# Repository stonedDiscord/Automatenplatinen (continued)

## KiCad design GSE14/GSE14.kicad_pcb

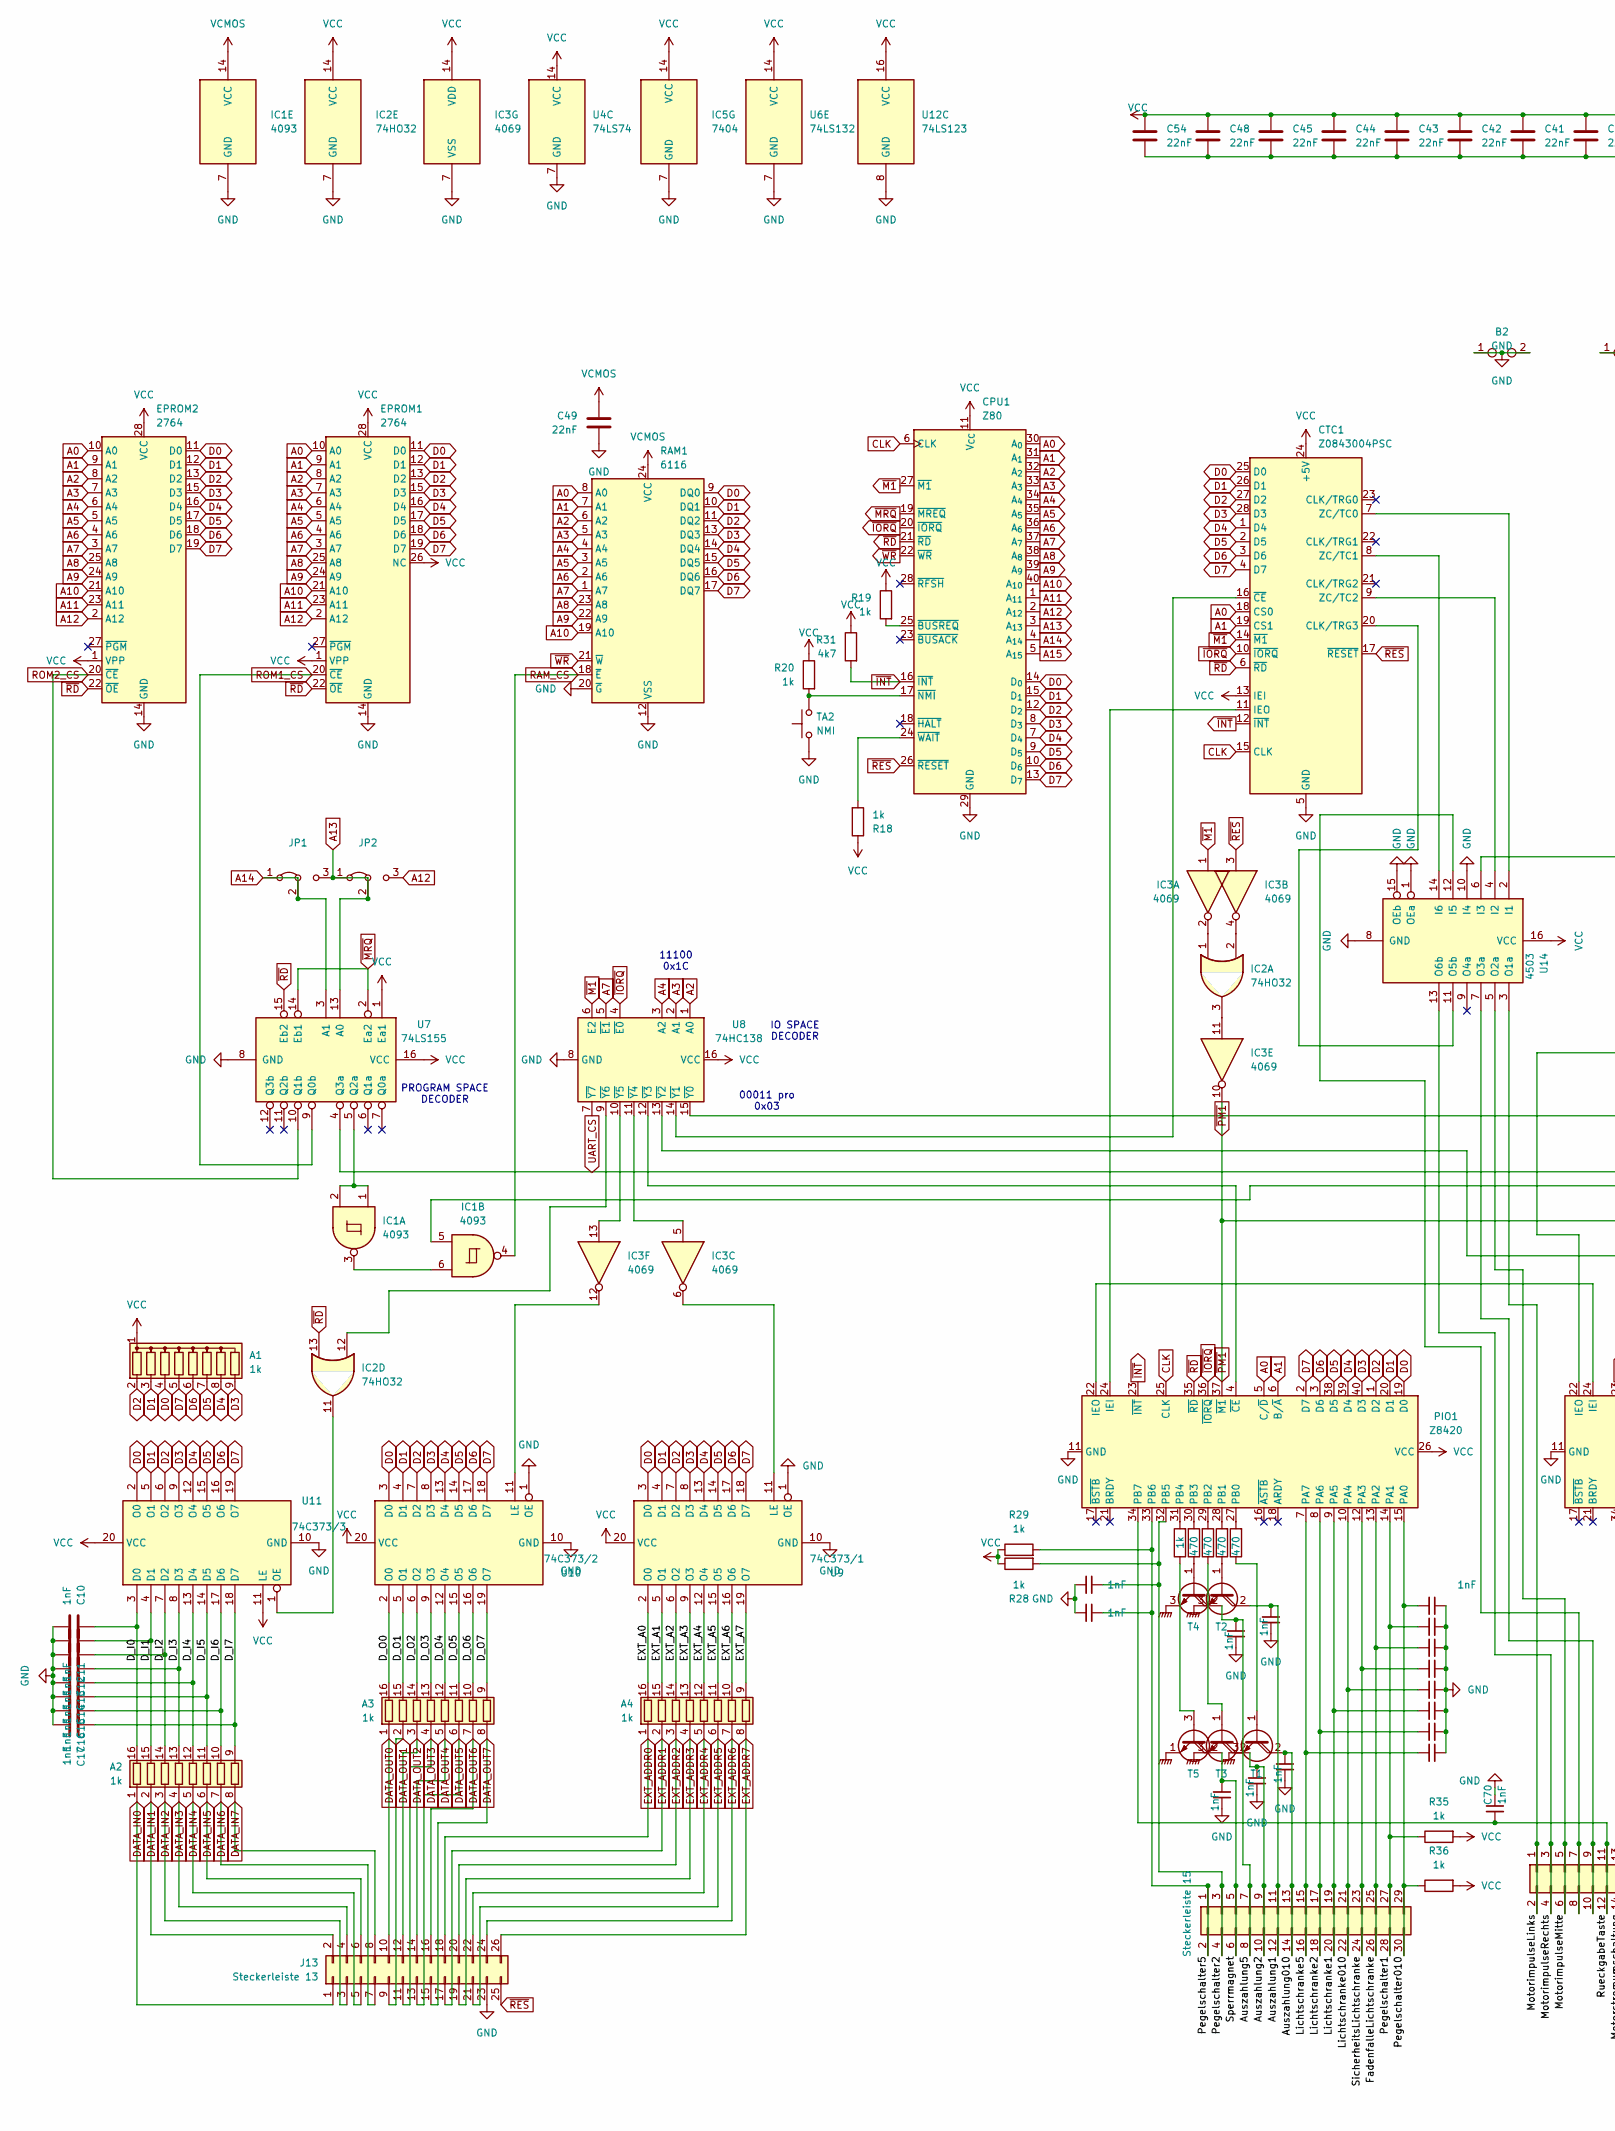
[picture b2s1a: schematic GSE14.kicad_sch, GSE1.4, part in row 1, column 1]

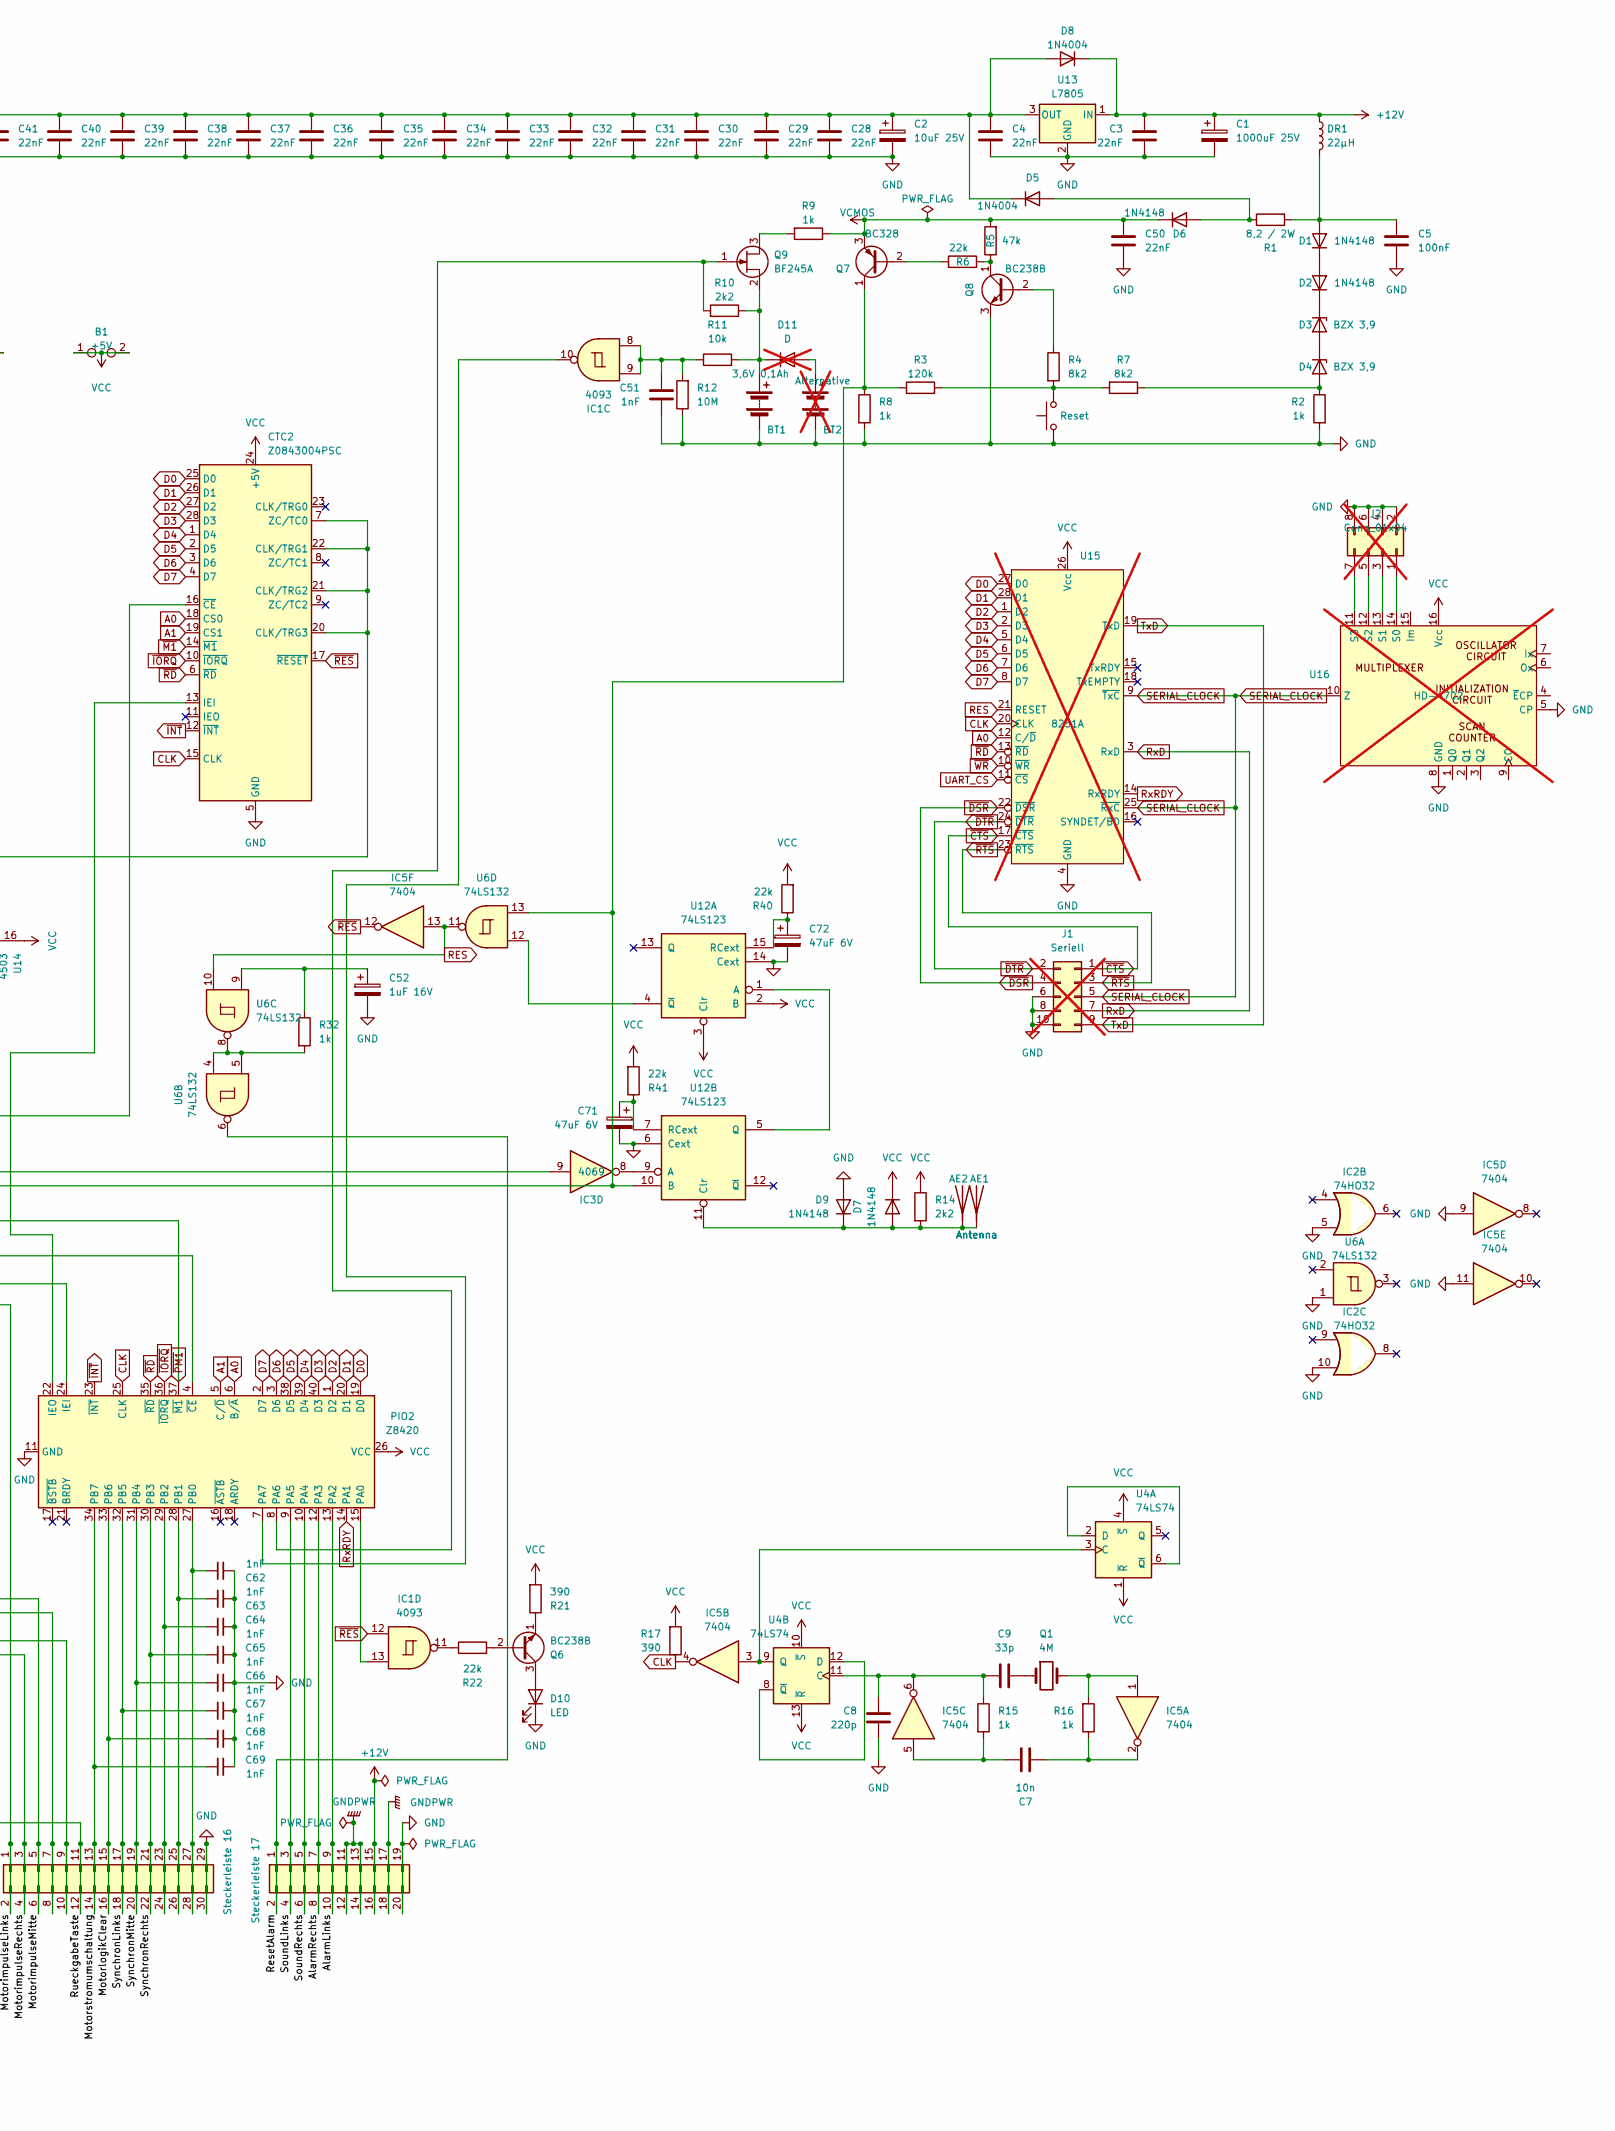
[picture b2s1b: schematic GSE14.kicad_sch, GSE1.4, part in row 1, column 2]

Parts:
A1: 1k; R_Array_SIP9
A2, A3, A4: 1k; DIP-16_W7.62mm
AE1, AE2: Antenna; TestPoint_Bridge_Pitch6.35mm_Drill1.3mm
B1: +5V; TestPoint_2Pads_Pitch5.08mm_Drill1.3mm
B2: GND; TestPoint_2Pads_Pitch5.08mm_Drill1.3mm
BT1: 3,6V 0,1Ah; Mempac
BT2: Alternative; Battery_Panasonic_CR2032-HFN_Horizontal_CircularHoles; not fitted
C1: 1000uF 25V; CP_Axial_L29.0mm_D10.0mm_P35.00mm_Horizontal
C2: 10uF 25V; CP_Radial_D6.3mm_P2.50mm
C3, C4, C28, C29, C30, C31, C32, C33, C34, C35, C36, C37, C38, C39, C40, C41, C42, C43, C44, C45, C48, C49, C50, C54: 22nF; C_Rect_L7.0mm_W2.0mm_P5.00mm
C5: 100nF; C_Rect_L7.0mm_W2.0mm_P5.00mm
C7: 10n; C_Disc_D4.3mm_W1.9mm_P5.00mm
C8: 220p; C_Disc_D4.3mm_W1.9mm_P5.00mm
C9: 33p; C_Disc_D4.3mm_W1.9mm_P5.00mm
C10, C11, C12, C13, C14, C15, C16, C17: 1nF; C_Disc_D4.3mm_W1.9mm_P5.00mm
C18, C19, C20, C21, C22, C23, C24, C25, C55, C56, C57, C58, C59, C60, C61, C62, C63, C64, C65, C66, C67, C68, C69, C70: 1nF; C_Disc_D5.0mm_W2.5mm_P5.00mm
C51: 1nF; C_Rect_L7.0mm_W2.0mm_P5.00mm
C52: 1uF 16V; CP_Radial_Tantal_D4.5mm_P5.00mm
C71, C72: 47uF 6V; CP_Radial_Tantal_D4.5mm_P5.00mm
CPU1: Z80; DIP-40_W15.24mm
CTC1, CTC2: Z0843004PSC; DIP-28_W15.24mm
D1, D2, D6, D7, D9: 1N4148; D_DO-35_SOD27_P12.70mm_Horizontal
D3, D4: BZX 3,9; D_DO-35_SOD27_P12.70mm_Horizontal
D5, D8: 1N4004; D_DO-35_SOD27_P12.70mm_Horizontal
D10: LED; LED_D5.0mm
D11: D; D_DO-35_SOD27_P7.62mm_Horizontal; not fitted
DR1: 22µH; L_Axial_L7.0mm_D3.3mm_P12.70mm_Horizontal_Fastron_MICC
EPROM1, EPROM2: 2764; DIP-28_W15.24mm
IC1: 4093; DIP-14_W7.62mm
IC2: 74HO32; DIP-14_W7.62mm
IC3: 4069; DIP-14_W7.62mm
IC5: 7404; DIP-14_W7.62mm
J1: Seriell; IDC-Header_2x05_P2.54mm_Vertical; not fitted
J2: Conn_01x04; PinHeader_2x04_P2.54mm_Vertical; not fitted
J13: Steckerleiste 13; IDC-Header_2x13_P2.54mm_Vertical
J15: Steckerleiste 15; PinHeader_2x15_P2.54mm_Vertical
J16: Steckerleiste 16; PinHeader_2x15_P2.54mm_Vertical
J17: Steckerleiste 17; PinHeader_2x10_P2.54mm_Vertical
JP1, JP2: Jumper_3_Bridged12
PIO1, PIO2: Z8420; DIP-40_W15.24mm
Q1: 4M; Crystal_HC49-U_Vertical
Q6, Q8: BC238B; TO-92
Q7: BC328; TO-92
Q9: BF245A; TO-92
R1: 8,2 / 2W; R_Axial_DIN0516_L15.5mm_D5.0mm_P30.48mm_Horizontal
R2, R8, R9, R15, R16, R18, R19, R20, R27, R28, R29, R32, R35, R36: 1k; R_Axial_DIN0309_L9.0mm_D3.2mm_P12.70mm_Horizontal
R3: 120k; R_Axial_DIN0309_L9.0mm_D3.2mm_P12.70mm_Horizontal
R4, R7: 8k2; R_Axial_DIN0309_L9.0mm_D3.2mm_P12.70mm_Horizontal
R5: 47k; R_Axial_DIN0309_L9.0mm_D3.2mm_P12.70mm_Horizontal
R6, R22, R40, R41: 22k; R_Axial_DIN0309_L9.0mm_D3.2mm_P12.70mm_Horizontal
R10, R14: 2k2; R_Axial_DIN0309_L9.0mm_D3.2mm_P12.70mm_Horizontal
R11: 10k; R_Axial_DIN0309_L9.0mm_D3.2mm_P12.70mm_Horizontal
R12: 10M; R_Axial_DIN0309_L9.0mm_D3.2mm_P12.70mm_Horizontal
R17, R21: 390; R_Axial_DIN0309_L9.0mm_D3.2mm_P12.70mm_Horizontal
R23, R24, R25, R26: 470; R_Axial_DIN0309_L9.0mm_D3.2mm_P12.70mm_Horizontal
R31: 4k7; R_Axial_DIN0309_L9.0mm_D3.2mm_P12.70mm_Horizontal
RAM1: 6116; DIP-24_18.0mmx34.29mm_W15.24mm
T1, T2, T3, T4: BDX 53 C; TO-220-3_Vertical
T5: BD 675; TO-251-3_Vertical
TA1: Reset; SW_PUSH_6mm
TA2: NMI; SW_PUSH_6mm
U4: 74LS74; DIP-14_W7.62mm
U6: 74LS132; DIP-14_W7.62mm
U7: 74LS155; DIP-16_W7.62mm
U8: 74HC138; DIP-16_W7.62mm
U9: 74C373/1; DIP-20_W7.62mm
U10: 74C373/2; DIP-20_W7.62mm
U11: 74C373/3; DIP-20_W7.62mm
U12: 74LS123; DIP-16_W7.62mm
U13: L7805; TO-220-3_Horizontal_TabDown
U14: 4503; DIP-16_W7.62mm
U15: 8251A; DIP-28_W15.24mm; not fitted
U16: HD-4702; DIP-16_W7.62mm; not fitted

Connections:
+12V: C1.1, C3.1, D8.1 (K), DR1.1, J17.15, J17.16, U13.1 (IN)
/AlarmLinks: J17.9, J17.10, PIO2.13 (PA2)
/AlarmRechts: J17.7, J17.8, PIO2.12 (PA3)
/Auszahlung1: C56.1, J15.11, J15.12, T2.2 (C)
/Auszahlung2: C57.1, J15.9, J15.10, T3.2 (C)
/Auszahlung5: C58.1, J15.7, J15.8, T4.2 (C)
/Auszahlung010: C55.2, J15.13, J15.14, T1.2 (C)
/D_I0: A2.16 (R1.2), C10.1, U11.3 (D0)
/D_I1: A2.15 (R2.2), C11.1, U11.4 (D1)
/D_I2: A2.14 (R3.2), C12.1, U11.7 (D2)
/D_I3: A2.13 (R4.2), C13.1, U11.8 (D3)
/D_I4: A2.12 (R5.2), C14.1, U11.13 (D4)
/D_I5: A2.11 (R6.2), C15.1, U11.14 (D5)
/D_I6: A2.10 (R7.2), C16.1, U11.17 (D6)
/D_I7: A2.9 (R8.2), C17.1, U11.18 (D7)
/D_O0: A3.16 (R1.2), U10.2 (O0)
/D_O1: A3.15 (R2.2), U10.5 (O1)
/D_O2: A3.14 (R3.2), U10.6 (O2)
/D_O3: A3.13 (R4.2), U10.9 (O3)
/D_O4: A3.12 (R5.2), U10.12 (O4)
/D_O5: A3.11 (R6.2), U10.15 (O5)
/D_O6: A3.10 (R7.2), U10.16 (O6)
/D_O7: A3.9 (R8.2), U10.19 (O7)
/EXT_A0: A4.16 (R1.2), U9.2 (O0)
/EXT_A1: A4.15 (R2.2), U9.5 (O1)
/EXT_A2: A4.14 (R3.2), U9.6 (O2)
/EXT_A3: A4.13 (R4.2), U9.9 (O3)
/EXT_A4: A4.12 (R5.2), U9.12 (O4)
/EXT_A5: A4.11 (R6.2), U9.15 (O5)
/EXT_A6: A4.10 (R7.2), U9.16 (O6)
/EXT_A7: A4.9 (R8.2), U9.19 (O7)
/FadenfalleLichtschranke: C20.1, J15.25, J15.26, PIO1.13 (PA2)
/Lichtschranke1: C23.1, J15.19, J15.20, PIO1.9 (PA5)
/Lichtschranke2: C24.1, J15.17, J15.18, PIO1.8 (PA6)
/Lichtschranke5: C25.1, J15.15, J15.16, PIO1.7 (PA7)
/Lichtschranke010: C22.1, J15.21, J15.22, PIO1.10 (PA4)
/MotorimpulseLinks: J16.1, J16.2, U14.3 (O1a)
/MotorimpulseMitte: J16.5, J16.6, U14.5 (O2a)
/MotorimpulseRechts: J16.3, J16.4, U14.13 (O6b)
/MotorlogikClear: C68.1, J16.15, J16.16, PIO2.33 (PB6)
/Motorstromumschaltung: C69.1, J16.13, J16.14, PIO2.34 (PB7)
/Pegelschalter1: C19.1, J15.27, J15.28, PIO1.14 (PA1), R35.1
/Pegelschalter2: C60.1, J15.3, J15.4, PIO1.32 (PB5), R28.2
/Pegelschalter5: C61.1, J15.1, J15.2, PIO1.33 (PB6), R29.2
/Pegelschalter010: C18.1, J15.29, J15.30, PIO1.15 (PA0), R36.1
/ResetAlarm: J17.1, J17.2, U6.6
/RueckgabeTaste: C70.1, J16.11, J16.12, PIO1.34 (PB7)
/SicherheitsLichtschranke: C21.1, J15.23, J15.24, PIO1.12 (PA3)
/SoundLinks: J17.3, J17.4, PIO2.9 (PA5)
/SoundRechts: J17.5, J17.6, PIO2.10 (PA4)
/Sperrmagnet: C59.1, J15.5, J15.6, T5.2 (C)
/SynchronLinks: C67.1, J16.17, J16.18, PIO2.32 (PB5)
/SynchronMitte: C66.1, J16.19, J16.20, PIO2.31 (PB4)
/SynchronRechts: C65.1, J16.21, J16.22, PIO2.30 (PB3)
A0: CPU1.30 (A_{0}), CTC1.18 (CS0), CTC2.18 (CS0), EPROM1.10 (A0), EPROM2.10 (A0), PIO1.5 (C/~D), PIO2.6 (B/~A), RAM1.8 (A0), U15.12 (C/~D)
A1: CPU1.31 (A_{1}), CTC1.19 (CS1), CTC2.19 (CS1), EPROM1.9 (A1), EPROM2.9 (A1), PIO1.6 (B/~A), PIO2.5 (C/~D), RAM1.7 (A1)
A2: CPU1.32 (A_{2}), EPROM1.8 (A2), EPROM2.8 (A2), RAM1.6 (A2), U8.1 (A0)
A3: CPU1.33 (A_{3}), EPROM1.7 (A3), EPROM2.7 (A3), RAM1.5 (A3), U8.2 (A1)
A4: CPU1.34 (A_{4}), EPROM1.6 (A4), EPROM2.6 (A4), RAM1.4 (A4), U8.3 (A2)
A5: CPU1.35 (A_{5}), EPROM1.5 (A5), EPROM2.5 (A5), RAM1.3 (A5)
A6: CPU1.36 (A_{6}), EPROM1.4 (A6), EPROM2.4 (A6), RAM1.2 (A6)
A7: CPU1.37 (A_{7}), EPROM1.3 (A7), EPROM2.3 (A7), RAM1.1 (A7), U8.5 (~E1)
A8: CPU1.38 (A_{8}), EPROM1.25 (A8), EPROM2.25 (A8), RAM1.23 (A8)
A9: CPU1.39 (A_{9}), EPROM1.24 (A9), EPROM2.24 (A9), RAM1.22 (A9)
A10: CPU1.40 (A_{10}), EPROM1.21 (A10), EPROM2.21 (A10), RAM1.19 (A10)
A11: CPU1.1 (A_{11}), EPROM1.23 (A11), EPROM2.23 (A11)
A12: CPU1.2 (A_{12}), EPROM1.2 (A12), EPROM2.2 (A12), JP2.3 (B)
A13: CPU1.3 (A_{13}), JP1.3 (B), JP2.1 (A), JP2.2 (C), U7.13 (A0)
A14: CPU1.4 (A_{14}), JP1.1 (A), JP1.2 (C), U7.3 (A1)
A15: CPU1.5 (A_{15})
CLK: CPU1.6 (CLK), CTC1.15 (CLK), CTC2.15 (CLK), IC5.4, PIO1.25 (CLK), PIO2.25 (CLK), R17.1, U15.20 (CLK)
D0: A1.4 (R3), CPU1.14 (D_{0}), CTC1.25 (D0), CTC2.25 (D0), EPROM1.11 (D0), EPROM2.11 (D0), PIO1.19 (D0), PIO2.19 (D0), RAM1.9 (DQ0), U9.3 (D0), U10.3 (D0), U11.2 (O0), U15.27 (D0)
D1: A1.3 (R2), CPU1.15 (D_{1}), CTC1.26 (D1), CTC2.26 (D1), EPROM1.12 (D1), EPROM2.12 (D1), PIO1.20 (D1), PIO2.20 (D1), RAM1.10 (DQ1), U9.4 (D1), U10.4 (D1), U11.5 (O1), U15.28 (D1)
D2: A1.2 (R1), CPU1.12 (D_{2}), CTC1.27 (D2), CTC2.27 (D2), EPROM1.13 (D2), EPROM2.13 (D2), PIO1.1 (D2), PIO2.1 (D2), RAM1.11 (DQ2), U9.7 (D2), U10.7 (D2), U11.6 (O2), U15.1 (D2)
D3: A1.9 (R8), CPU1.8 (D_{3}), CTC1.28 (D3), CTC2.28 (D3), EPROM1.15 (D3), EPROM2.15 (D3), PIO1.40 (D3), PIO2.40 (D3), RAM1.13 (DQ3), U9.8 (D3), U10.8 (D3), U11.9 (O3), U15.2 (D3)
D4: A1.8 (R7), CPU1.7 (D_{4}), CTC1.1 (D4), CTC2.1 (D4), EPROM1.16 (D4), EPROM2.16 (D4), PIO1.39 (D4), PIO2.39 (D4), RAM1.14 (DQ4), U9.13 (D4), U10.13 (D4), U11.12 (O4), U15.5 (D4)
D5: A1.7 (R6), CPU1.9 (D_{5}), CTC1.2 (D5), CTC2.2 (D5), EPROM1.17 (D5), EPROM2.17 (D5), PIO1.38 (D5), PIO2.38 (D5), RAM1.15 (DQ5), U9.14 (D5), U10.14 (D5), U11.15 (O5), U15.6 (D5)
D6: A1.6 (R5), CPU1.10 (D_{6}), CTC1.3 (D6), CTC2.3 (D6), EPROM1.18 (D6), EPROM2.18 (D6), PIO1.3 (D6), PIO2.3 (D6), RAM1.16 (DQ6), U9.17 (D6), U10.17 (D6), U11.16 (O6), U15.7 (D6)
D7: A1.5 (R4), CPU1.13 (D_{7}), CTC1.4 (D7), CTC2.4 (D7), EPROM1.19 (D7), EPROM2.19 (D7), PIO1.2 (D7), PIO2.2 (D7), RAM1.17 (DQ7), U9.18 (D7), U10.18 (D7), U11.19 (O7), U15.8 (D7)
DATA_IN0: A2.1 (R1.1), J13.1
DATA_IN1: A2.2 (R2.1), J13.2
DATA_IN2: A2.3 (R3.1), J13.3
DATA_IN3: A2.4 (R4.1), J13.4
DATA_IN4: A2.5 (R5.1), J13.5
DATA_IN5: A2.6 (R6.1), J13.6
DATA_IN6: A2.7 (R7.1), J13.7
DATA_IN7: A2.8 (R8.1), J13.8
DATA_OUT0: A3.1 (R1.1), J13.10
DATA_OUT1: A3.2 (R2.1), J13.9
DATA_OUT2: A3.3 (R3.1), J13.12
DATA_OUT3: A3.4 (R4.1), J13.11
DATA_OUT4: A3.5 (R5.1), J13.14
DATA_OUT5: A3.6 (R6.1), J13.13
DATA_OUT6: A3.7 (R7.1), J13.16
DATA_OUT7: A3.8 (R8.1), J13.15
EXT_ADDR0: A4.1 (R1.1), J13.18
EXT_ADDR1: A4.2 (R2.1), J13.17
EXT_ADDR2: A4.3 (R3.1), J13.20
EXT_ADDR3: A4.4 (R4.1), J13.19
EXT_ADDR4: A4.5 (R5.1), J13.22
EXT_ADDR5: A4.6 (R6.1), J13.21
EXT_ADDR6: A4.7 (R7.1), J13.24
EXT_ADDR7: A4.8 (R8.1), J13.26
GND: B2.1, B2.2, BT1.2 (-), BT2.2 (-), C1.2, C2.2, C3.2, C4.2, C5.2, C8.2, C10.2, C11.2, C12.2, C13.2, C14.2, C15.2, C16.2, C17.2, C18.2, C19.2, C20.2, C21.2, C22.2, C23.2, C24.2, C25.2, C28.2, C29.2, C30.2, C31.2, C32.2, C33.2, C34.2, C35.2, C36.2, C37.2, C38.2, C39.2, C40.2, C41.2, C42.2, C43.2, C44.2, C45.2, C48.2, C49.2, C50.2, C51.2, C52.2, C54.2, C55.1, C56.2, C57.2, C58.2, C59.2, C60.2, C61.2, C62.2, C63.2, C64.2, C65.2, C66.2, C67.2, C68.2, C69.2, C70.2, C71.2, C72.2, CPU1.29 (GND), CTC1.5 (GND), CTC2.5 (GND), D9.2 (A), D10.1 (K), EPROM1.14 (GND), EPROM2.14 (GND), IC1.7 (GND), IC2.5, IC2.7 (GND), IC2.10, IC3.7 (VSS), IC5.7 (GND), IC5.9, IC5.11, J1.6, J1.8, J1.10, J2.2, J2.4, J2.6, J2.8, J13.23, J16.29, J16.30, J17.19, J17.20, PIO1.11 (GND), PIO2.11 (GND), Q8.3 (E), R2.2, R8.2, R12.1, RAM1.12 (VSS), RAM1.20 (~G), TA1.1, TA2.1, U4.7 (GND), U6.1, U6.7 (GND), U7.8 (GND), U8.8 (GND), U9.1 (OE), U9.10 (GND), U10.1 (OE), U10.10 (GND), U11.10 (GND), U12.6 (Cext), U12.8 (GND), U12.14 (Cext), U13.2 (GND), U14.1 (OEa), U14.8 (GND), U14.10 (I4), U14.15 (OEb), U15.4 (GND), U16.5 (CP), U16.8 (GND)
GNDPWR: J17.11, J17.12, J17.13, J17.14, J17.17, J17.18, T1.3 (E), T2.3 (E), T3.3 (E), T4.3 (E), T5.1 (E)
unnamed: AE1.1 (A_1), AE2.1 (A_1), D7.2 (A), D9.1 (K), R14.2, U12.11 (Clr)
unnamed: BT1.1 (+), D11.1 (K), Q9.2 (S), R10.1, R11.2
unnamed: BT2.1 (+), D11.2 (A)
unnamed: C7.1, IC5.5, R15.2
unnamed: C7.2, IC5.2, R16.1
unnamed: C9.2, Q1.1
unnamed: C51.1, IC1.8, IC1.9, R11.1, R12.2
unnamed: C52.1, R32.1, U6.9
unnamed: CPU1.25 (~BUSREQ), R19.2
unnamed: CPU1.17 (~NMI), R20.2, TA2.2
unnamed: CPU1.24 (~WAIT), R18.2
unnamed: CTC1.20 (CLK/TRG3), U14.11 (O5b)
unnamed: CTC1.11 (IEO), PIO1.24 (IEI)
unnamed: CTC1.7 (ZC/TC0), U14.2 (I1)
unnamed: CTC1.8 (ZC/TC1), U14.14 (I6)
unnamed: CTC1.9 (ZC/TC2), U14.4 (I2)
unnamed: CTC1.16 (~CE), U8.14 (~Y1)
unnamed: CTC2.7 (ZC/TC0), CTC2.20 (CLK/TRG3), CTC2.21 (CLK/TRG2), CTC2.22 (CLK/TRG1), U14.6 (I3)
unnamed: CTC2.13 (IEI), PIO2.22 (IEO)
unnamed: CTC2.16 (~CE), U8.15 (~Y0)
unnamed: C5.1, D1.2 (A), DR1.2, R1.2
unnamed: D1.1 (K), D2.2 (A)
unnamed: D2.1 (K), D3.1 (K)
unnamed: D3.2 (A), D4.1 (K)
unnamed: D4.2 (A), R2.1, R7.1
unnamed: D5.2 (A), D6.2 (A), R1.1
unnamed: D10.2 (A), Q6.3 (C)
unnamed: IC1.3, IC1.6
unnamed: IC1.11, R22.1
unnamed: IC2.1, IC3.2
unnamed: IC2.2, IC3.4
unnamed: IC2.3, IC3.11
unnamed: IC5.1, Q1.2, R16.2
unnamed: J2.1, U16.14 (S0)
unnamed: J2.3, U16.13 (S1)
unnamed: J2.5, U16.12 (S2)
unnamed: J2.7, U16.11 (S3)
unnamed: J16.7, J16.8, U14.12 (I5)
unnamed: J16.9, J16.10, U14.7 (O3a)
unnamed: C64.1, J16.23, J16.24, PIO2.29 (PB2)
unnamed: C63.1, J16.25, J16.26, PIO2.28 (PB1)
unnamed: C62.1, J16.27, J16.28, PIO2.27 (PB0)
unnamed: PIO1.22 (IEO), PIO2.24 (IEI)
unnamed: PIO1.27 (PB0), R23.2
unnamed: PIO1.28 (PB1), R24.2
unnamed: PIO1.29 (PB2), R25.2
unnamed: PIO1.30 (PB3), R26.2
unnamed: PIO1.31 (PB4), R27.2
unnamed: PIO1.4 (~CE), U8.12 (~Y3)
unnamed: IC1.13, PIO2.15 (PA0)
unnamed: PIO2.8 (PA6), Q9.1 (G), R10.2
unnamed: IC1.10, PIO2.7 (PA7)
unnamed: PIO2.4 (~CE), U8.13 (~Y2)
unnamed: Q6.2 (B), R22.2
unnamed: Q6.1 (E), R21.1
unnamed: Q7.2 (B), R6.2
unnamed: IC1.5, Q7.1 (C), R3.1, R8.1, U6.13, U12.10 (B)
unnamed: Q8.2 (B), R4.1
unnamed: Q8.1 (C), R5.1, R6.1
unnamed: Q9.3 (D), R9.2
unnamed: R3.2, R4.2, R7.2, TA1.2
unnamed: R32.2, U6.4, U6.5, U6.8
unnamed: R23.1, T1.1 (B)
unnamed: R24.1, T2.1 (B)
unnamed: R25.1, T3.1 (B)
unnamed: R26.1, T4.1 (B)
unnamed: R27.1, T5.3 (B)
unnamed: IC5.3, U4.3 (C), U4.9 (Q)
unnamed: U4.2 (D), U4.6 (~Q)
unnamed: C8.1, C9.1, IC5.6, R15.1, U4.11 (C)
unnamed: U4.8 (~Q), U4.12 (D)
unnamed: IC1.1, IC1.2, U7.5 (Q2a)
unnamed: IC3.9, U7.4 (Q3a)
unnamed: IC3.5, U8.11 (~Y4)
unnamed: IC3.13, U8.10 (~Y5)
unnamed: IC2.12, U8.9 (~Y6)
unnamed: IC3.6, U9.11 (LE)
unnamed: IC3.12, U10.11 (LE)
unnamed: IC2.11, U11.1 (OE)
unnamed: U12.1 (A), U12.5 (Q)
unnamed: C72.1, R40.1, U12.15 (RCext)
unnamed: U6.12, U12.4 (~Q)
unnamed: IC3.8, U12.9 (A)
unnamed: C71.1, R41.1, U12.7 (RCext)
RAM_CS: IC1.4, RAM1.18 (~E)
RES: IC5.13, U6.10, U6.11, U15.21 (RESET)
ROM1_CS: EPROM1.20 (~CE), U7.9 (Q0b)
ROM2_CS: EPROM2.20 (~CE), U7.10 (Q1b)
RxD: J1.7, U15.3 (RxD)
RxRDY: PIO2.14 (PA1), U15.14 (RxRDY)
SERIAL_CLOCK: J1.5, U15.9 (~TxC), U15.25 (~RxC), U16.10 (Z)
TxD: J1.9, U15.19 (TxD)
UART_CS: U8.7 (~Y7), U15.11 (~CS)
VCC: A1.1 (common), B1.1, B1.2, C2.1, C4.1, C28.1, C29.1, C30.1, C31.1, C32.1, C33.1, C34.1, C35.1, C36.1, C37.1, C38.1, C39.1, C40.1, C41.1, C42.1, C43.1, C44.1, C45.1, C48.1, C54.1, CPU1.11 (V_{CC}), CTC1.13 (IEI), CTC1.24 (+5V), CTC2.24 (+5V), D5.1 (K), D7.1 (K), D8.2 (A), EPROM1.1 (VPP), EPROM1.26 (NC), EPROM1.28 (VCC), EPROM2.1 (VPP), EPROM2.28 (VCC), IC2.14 (VCC), IC3.14 (VDD), IC5.14 (VCC), PIO1.26 (VCC), PIO2.26 (VCC), R14.1, R17.2, R18.1, R19.1, R20.1, R21.2, R28.1, R29.1, R31.1, R35.2, R36.2, R40.2, R41.2, U4.1 (~R), U4.4 (~S), U4.10 (~S), U4.13 (~R), U4.14 (VCC), U6.14 (VCC), U7.1 (Ea1), U7.16 (VCC), U8.16 (VCC), U9.20 (VCC), U10.20 (VCC), U11.11 (LE), U11.20 (VCC), U12.2 (B), U12.3 (Clr), U12.16 (VCC), U13.3 (OUT), U14.16 (VCC), U15.26 (Vcc), U16.16 (Vcc)
VCMOS: C49.1, C50.1, D6.1 (K), IC1.14 (VCC), Q7.3 (E), R5.2, R9.1, RAM1.24 (VCC)
~CTS: J1.1, U15.17 (~CTS)
~DSR: J1.4, U15.22 (~DSR)
~DTR: J1.2, U15.24 (~DTR)
~INT: CPU1.16 (~INT), CTC1.12 (~INT), CTC2.12 (~INT), PIO1.23 (~INT), PIO2.23 (~INT), R31.2
~IORQ: CPU1.20 (~IORQ), CTC1.10 (~IORQ), CTC2.10 (~IORQ), PIO1.36 (~IORQ), PIO2.36 (~IORQ), U8.4 (~E0)
~M1: CPU1.27 (~M1), CTC1.14 (~M1), CTC2.14 (~M1), IC3.1, U8.6 (E2)
~MRQ: CPU1.19 (~MREQ), U7.2 (Ea2), U7.14 (Eb1)
~PM1: IC3.10, PIO1.37 (~M1), PIO2.37 (~M1)
~RD: CPU1.21 (~RD), CTC1.6 (~RD), CTC2.6 (~RD), EPROM1.22 (~OE), EPROM2.22 (~OE), IC2.13, PIO1.35 (~RD), PIO2.35 (~RD), U7.15 (Eb2), U15.13 (~RD)
~RES: CPU1.26 (~RESET), CTC1.17 (~RESET), CTC2.17 (~RESET), IC1.12, IC3.3, IC5.12, J13.25
~RTS: J1.3, U15.23 (~RTS)
~WR: CPU1.22 (~WR), RAM1.21 (~W), U15.10 (~WR)

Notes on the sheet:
11100 0x1C
00011 pro 0x03
PROGRAM SPACE DECODER
IO SPACE DECODER

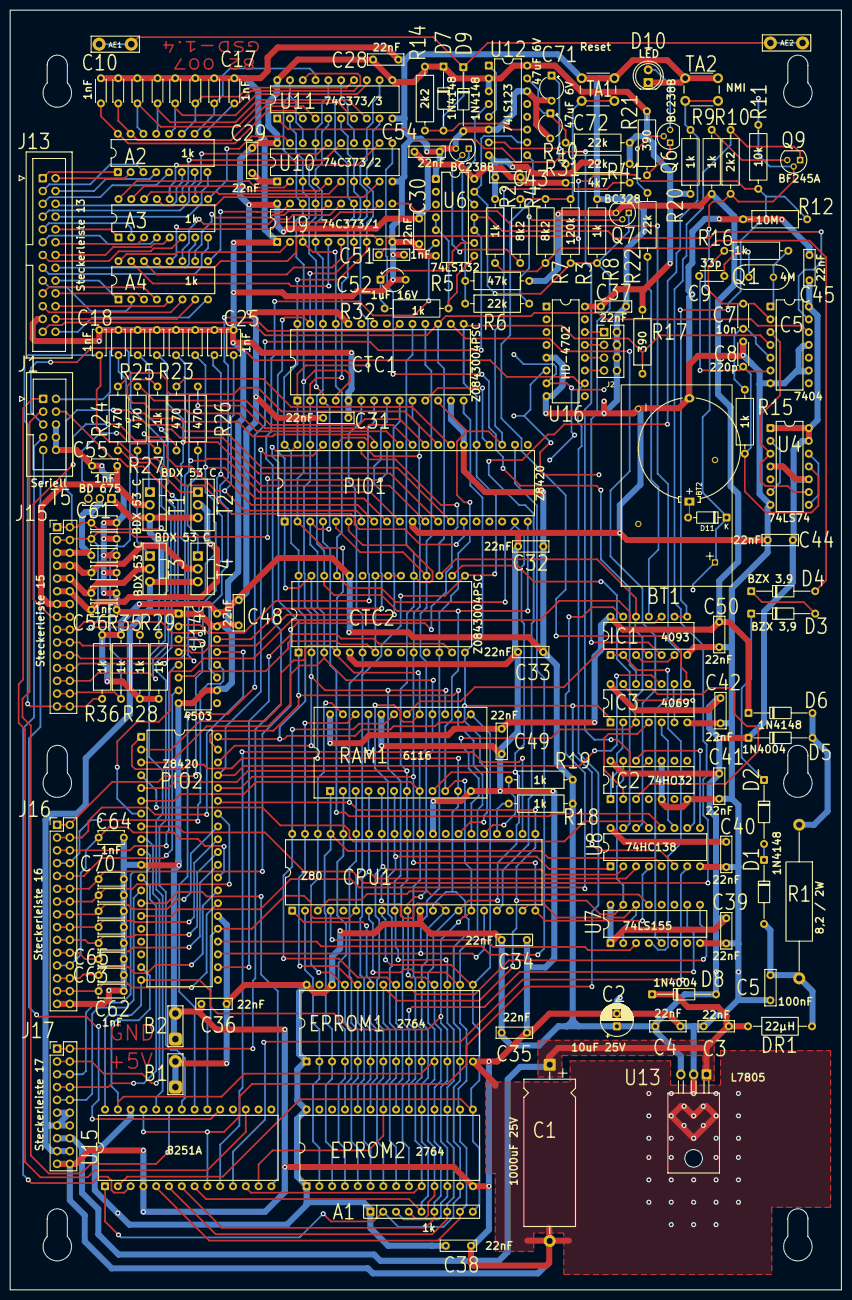
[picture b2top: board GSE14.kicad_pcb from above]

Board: 2 copper layers, 165.0 x 254.0 mm, 164 parts (0 on the bottom side), 211 nets.

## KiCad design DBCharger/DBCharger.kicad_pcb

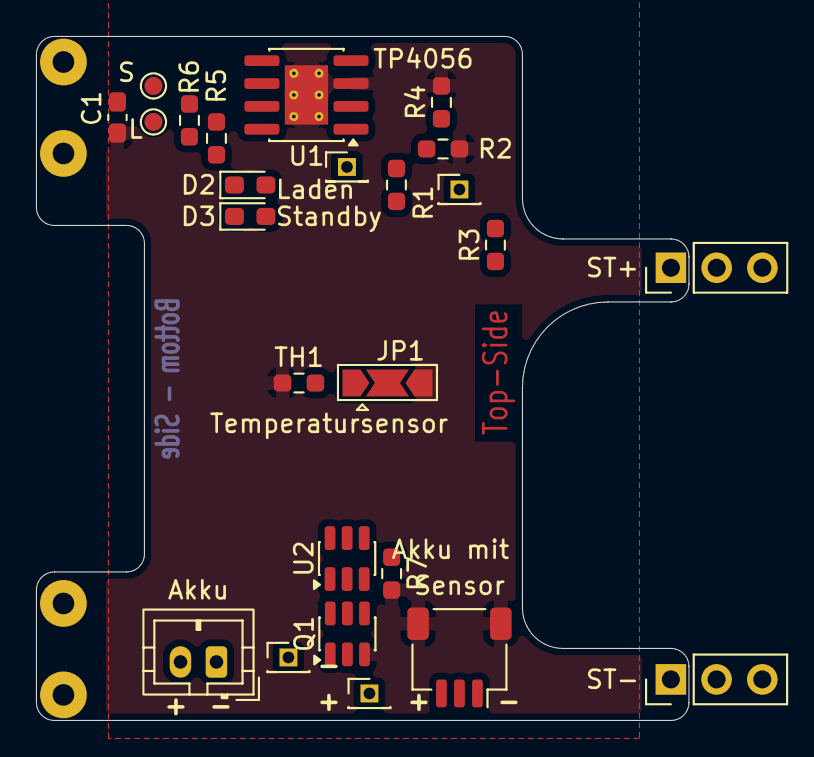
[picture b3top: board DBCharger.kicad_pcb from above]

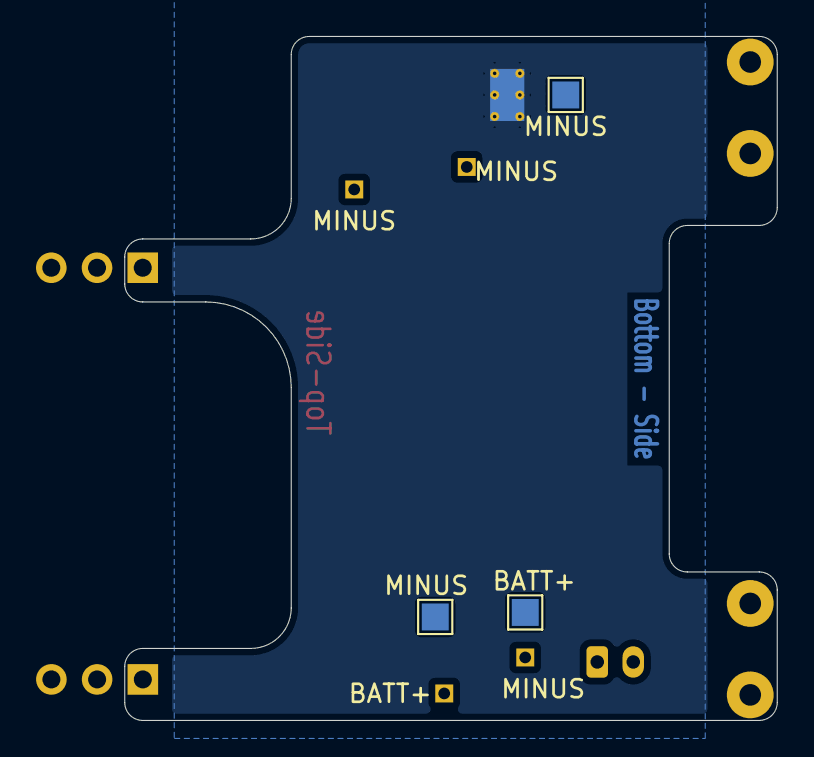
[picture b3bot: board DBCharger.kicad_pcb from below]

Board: 2 copper layers, 36.2 x 38.0 mm, 30 parts (4 on the bottom side), 17 nets, no tracks yet.

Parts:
C1: 10uF; C_0603_1608Metric_Pad1.08x0.95mm_HandSolder
D2: Laden; LED_0603_1608Metric_Pad1.05x0.95mm_HandSolder
D3: Standby; LED_0603_1608Metric_Pad1.05x0.95mm_HandSolder
J1: Akku; JST_PH_B2B-PH-K_1x02_P2.00mm_Vertical
J2: BATT+; PinHeader_1x01_P1.27mm_Vertical
J3: ST+; PinHeader_1x03_P2.54mm_Vertical
J4: ST-; PinHeader_1x03_P2.54mm_Vertical
J5: Akku mit; JST_SH_SM03B-SRSS-TB_1x03-1MP_P1.00mm_Horizontal
J6, J7, J8: MINUS; PinHeader_1x01_P1.27mm_Vertical
J9, J10: Conn_01x02; Battery_Cast
JP1: Sensor; SolderJumper-3_P2.0mm_Open_TrianglePad1.0x1.5mm
Q1: FS8205; SOT-23-6
R1, R2, R3: R; R_0603_1608Metric_Pad0.98x0.95mm_HandSolder
R4, R5, R6: 4,7k; R_0603_1608Metric_Pad0.98x0.95mm_HandSolder
R7: 1k; R_0603_1608Metric_Pad0.98x0.95mm_HandSolder
TH1: Temperatursensor; R_0603_1608Metric_Pad0.98x0.95mm_HandSolder
TP1: L; TestPoint_Pad_D1.0mm
TP2: S; TestPoint_Pad_D1.0mm
TP3: BATT+; TestPoint_Pad_1.5x1.5mm
TP4, TP5: MINUS; TestPoint_Pad_1.5x1.5mm
U1: TP4056; SOIC-8-1EP_3.9x4.9mm_P1.27mm_EP2.41x3.3mm_ThermalVias
U2: DW01A; SOT-23-6

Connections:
+BATT: C1.2, J1.2, J2.1 (Pin_1_1), J5.3, TP3.1 (1_1), U1.5 (BAT), U2.5 (VCC)
+NVRAM: J9.1, J10.1
-BATT: J1.1, J5.1, J6.1 (Pin_1_1), J7.1 (Pin_1_1), J8.1 (Pin_1_1), Q1.1 (D1), TP4.1 (1_1), TP5.1 (1_1), U2.6 (GND)
-NVRAM: J9.2, J10.2
/TEMP: J5.2, JP1.2 (C), R1.2, R2.1, U1.1 (TEMP)
GND: C1.1, J4.1, J4.2, J4.3, J5.MP (MountPin), JP1.3 (B), Q1.3 (S2), R2.2, R4.2, R7.2, TH1.1, U1.3 (GND), U1.9 (EPAD)
unnamed: D2.1 (K), R5.1
unnamed: D3.1 (K), R6.1
unnamed: JP1.1 (A), TH1.2
unnamed: Q1.6 (G1), U2.1 (OD)
unnamed: Q1.4 (G2), U2.3 (OC)
unnamed: R4.1, U1.2 (PROG)
unnamed: R5.2, TP1.1 (1_1), U1.7 (~CHRG)
unnamed: R6.2, TP2.1 (1_1), U1.6 (~STDBY)
unnamed: R7.1, U2.2 (CS)
VCC: D2.2 (A), D3.2 (A), R1.1, R3.2, U1.4 (V_{CC}), U1.8 (CE)
VDD: J3.1, J3.2, J3.3, R3.1
